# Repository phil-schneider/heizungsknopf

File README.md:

# Heizungsknopf – ein alter Gasofen bekommt einen Wochenplan

<table>
  <tr>
    <td align="center" valign="top" width="50%"></td>
    <td align="center" valign="top" width="50%"></td>
  </tr>
  <tr>
    <td align="center"><em>Heute: das Gasventil mit dem Drehknopf (✱ und 1–7)</em></td>
    <td align="center"><em>So soll es aussehen: Fotomontage mit dem Motoraufsatz (Erläuterung der Farben im Bild)</em></td>
  </tr>
</table>

Ein kleiner Motor dreht den Thermostatknopf eines Gas-Raumheizers, gesteuert von einem WLAN-Chip mit Wochenplan.
Am Ofen selbst wird nichts verändert: Der Aufsatz wird nur auf den vorhandenen Drehknopf gesteckt und lässt sich jederzeit wieder abziehen.

> [!WARNING]
> **Dieses Projekt ist noch in der Umsetzung und ungetestet.**
> Bisher wurde nichts davon gebaut oder am Ofen ausprobiert. Wer jetzt nachbaut, baut einen Entwurf nach.

## Projektstatus (Stand: November 2026)

| Bereich | Status |
|---|---|
| Idee und Messungen am Ofen | ✅ fertig |
| Platinen (Hauptplatine, Bedienteil) | ✅ entworfen · 📦 bestellt, noch nicht geliefert |
| Gehäuse und Motoraufsatz (3D-Druck) | ✅ entworfen · 📦 bestellt, noch nicht geliefert |
| Firmware | 🛠️ erste Version, muss an den Motoraufsatz angepasst werden |
| Zusammenbau | ⏳ noch nicht begonnen |
| Test am Ofen | ⏳ noch nicht begonnen |

Was noch fehlt, steht unter [Offene Punkte](#offene-punkte).

---

## Inhalt

1. [Projektstatus](#projektstatus-stand-november-2026)
2. [Warum gibt es dieses Projekt?](#warum-gibt-es-dieses-projekt)
3. [Was ist das Ziel?](#was-ist-das-ziel)
4. [Wie alles zusammenhängt](#wie-alles-zusammenhängt)
5. [Was liegt in diesem Repository?](#was-liegt-in-diesem-repository)
6. [Wie die einzelnen Teile funktionieren](#wie-die-einzelnen-teile-funktionieren)
7. [Nachbauen Schritt für Schritt](#nachbauen-schritt-für-schritt)
8. [Sicherheit](#sicherheit)
9. [Offene Punkte](#offene-punkte)
10. [Begriffe kurz erklärt](#begriffe-kurz-erklärt)

---

## Warum gibt es dieses Projekt?

Viele ältere Gas-Raumheizer (Gasöfen, Konvektoren) haben nur einen Drehknopf am Gasventil: ✱ für die Zündflamme und 1 bis 7 für die Temperatur. Eine Uhr oder einen Zeitplan gibt es nicht. Wer morgens in ein warmes Zimmer kommen will, muss abends den Knopf hochdrehen und heizt die ganze Nacht durch, oder er steht früh auf und dreht von Hand.

Moderne Thermostate kann man an so einen Ofen nicht einfach anschließen, und am Gasventil selbst darf und soll man als Laie nichts umbauen. Der einfachste sichere Weg ist deshalb: **Man lässt den Ofen, wie er ist, und dreht nur den Knopf automatisch**, so wie es ein Mensch auch tun würde.

## Was ist das Ziel?

- Der Ofen heizt nach einem **Wochenplan**, z. B. morgens um 6 Uhr auf Stufe 5, tagsüber Stufe 2, abends wieder Stufe 5.
- Man kann die Stufe jederzeit **am Ofen** (zwei Tasten und ein Display) oder **im Browser** (Handy, PC) ändern.
- Zusätzlich gibt es **Boost** (für eine Weile wärmer) und einen **Urlaubsmodus** (niedrige Stufe bis zu einem Rückkehrtag).
- Es braucht **keine Cloud und kein Home Assistant**. Der Knopf hat eine eigene kleine Webseite im Heimnetz.
- **Nichts am Gasofen wird umgebaut.** Der Motoraufsatz steckt auf dem Original-Knopf. Zieht man ihn ab, ist alles wie vorher.

---

## Wie alles zusammenhängt

Das System besteht aus **drei Baugruppen**, die mit Kabeln verbunden sind:

```mermaid
flowchart LR
    NT["12-V-Netzteil"] --> HP

    subgraph HP["Hauptplatine (im eigenen Gehäuse, neben dem Ofen)"]
        ESP["ESP32-C3<br/>WLAN, Uhr, Wochenplan"]
        TMC["TMC2209<br/>Motortreiber"]
        ESP --> TMC
    end

    BT["Bedienteil (an der Gittertür)<br/>Display · Tasten + und − · Raumtemperatur"]
    HP <-->|"normales Netzwerkkabel<br/>(RJ45, 1:1)"| BT

    TMC -->|"Motorkabel, 4 Adern"| MA

    subgraph MA["Motoraufsatz (auf dem Drehknopf)"]
        M["Schrittmotor NEMA17"] --> R["Ritzel"] --> Z["Kappe mit Zahnkranz"] --> K["Original-Drehknopf<br/>am Gasventil"]
    end

    DS["Ofenfühler DS18B20<br/>(optional)"] --> HP
    HANDY["Handy / PC im WLAN"] -.->|"Browser"| ESP
```

Falls das Diagramm nicht angezeigt wird, hier dasselbe als Skizze:

```
  12 V ──► ┌──────────────────┐   Netzwerkkabel   ┌─────────────────────┐
           │  HAUPTPLATINE    │◄─────────────────►│  BEDIENTEIL         │
 WLAN ◄──► │  ESP32-C3        │   (RJ45, 1:1)     │  Display, + / −,    │
           │  Motortreiber    │                   │  Temperatursensor   │
           └────────┬─────────┘                   └─────────────────────┘
                    │ Motorkabel (4 Adern)
                    ▼
           ┌──────────────────┐
           │  MOTORAUFSATZ    │   Motor ─► Ritzel ─► Zahnkranz-Kappe ─► Drehknopf
           └──────────────────┘
```

**So läuft es im Alltag ab:** Die Hauptplatine kennt die Uhrzeit (aus dem Internet) und den Wochenplan. Ist es Zeit für eine neue Stufe, dreht der Motor über zwei Zahnräder den Knopf auf die richtige Position. Das Display am Bedienteil zeigt die aktuelle Stufe, die Raumtemperatur und den nächsten Wechsel. Drückt man + oder −, dreht der Knopf sofort weiter, und diese Einstellung gilt bis zum nächsten Eintrag im Wochenplan.

---

## Was liegt in diesem Repository?

| Ordner | Inhalt | Wofür? |
|---|---|---|
| [`platinen/hauptplatine/`](platinen/hauptplatine) | `hauptplatine_Gerber.zip`, `hauptplatine_BOM_JLCPCB.csv`, `hauptplatine_CPL_JLCPCB.csv`, `hauptplatine.kicad_pcb` | Hauptplatine bestellen (fertig bestückt) oder in KiCad ansehen |
| [`platinen/bedienteil/`](platinen/bedienteil) | dieselben vier Dateien für das Bedienteil | Bedienplatine bestellen |
| [`3d-druck/stl/`](3d-druck/stl) | 12 STL-Dateien | Gehäuse und Motoraufsatz bei einem Druckdienst drucken lassen |
| [`3d-druck/step/`](3d-druck/step) | dieselben 12 Teile als STEP | Teile in einem CAD-Programm ansehen oder anpassen |
| [`firmware/`](firmware) | `heizung.yaml`, `heizung_logik.h`, `heizung_ui.js`, `secrets.example.yaml` | Software für den ESP32 (ESPHome) |
| [`bilder/`](bilder) | Vorschaubilder der Platinen und Druckteile | für diese Anleitung |

Was die Dateiendungen bedeuten, steht unten unter [Begriffe kurz erklärt](#begriffe-kurz-erklärt).

---

## Wie die einzelnen Teile funktionieren

### 1. Der Motoraufsatz: Wie der Knopf gedreht wird

Der Ofen hat ein Gasventil vom Typ **SIT 710 Minisit ECO**. Sein Drehknopf (Ø 35,7 mm, 19,4 mm hoch, 16 kleine Rippen am Rand) dreht von ✱ bis 7 um etwa **295°**, an beiden Enden ist ein fester Anschlag.

Die naheliegende Idee, den Motor einfach oben auf den Knopf zu setzen, passt nicht: Über dem Knopf sind nur **40,5 mm Platz** bis zu einem Querträger. Deshalb wird über Zahnräder gedreht:

```
        Seitenansicht, vereinfacht

     Ritzel ┐      ┌ Zahnkranz an der Kappe
            ▼      ▼
          ┌───┐ ┌───────────┐
          │▓▓▓│ │▓  Kappe  ▓│   ◄─ steckt auf dem Original-Knopf
     ═════╪═══╪═╪═══════════╪══════  Halter (liegt auf der Blende des Ventils)
          │   │ │   Knopf   │
      ┌───┴───┴─┐───────────────────
      │  Motor  │    Blende / Gasventil
      │ NEMA17  │
      └─────────┘
       (hängt vor der Blende)
```

- **Kappe mit Zahnkranz** (`motor_kappe_zahnkranz`): wird von oben auf den Knopf gesteckt. Innen hat sie 16 Nuten, in die die Rippen des Knopfs greifen, so dreht der Knopf mit, ohne zu rutschen. Außen sitzt ein Zahnkranz mit 34 Zähnen. Zwei kleine Madenschrauben sichern die Kappe zusätzlich.
- **Ritzel** (`motor_ritzel`): ein kleines Zahnrad mit 22 Zähnen auf der Motorwelle.
- **Motorhalter** (`motor_halter`): liegt wie ein Rahmen auf der Blende, ein Loch umschließt den Knopf und hält alles in Position. Der Motor hängt senkrecht davor. Zwei Stellschrauben drücken gegen die Vorderseite der Blende, damit der Halter waagerecht steht und nicht kippt.
- **Übersetzung:** 34 : 22, also etwa 1,55 : 1. Der Motor dreht etwas weiter als der Knopf, dafür hat er mehr Kraft am Knopf.
- **Von Hand bedienen:** Kappe nach oben abziehen (sie passt dabei noch unter den Querträger), oder bei ausgeschaltetem Motor einfach am Zahnkranz drehen.

Alle Maße wurden am echten Ofen gemessen. **Für einen anderen Ofen müssen die Teile angepasst werden** (z. B. in FreeCAD, Fusion oder Onshape über die STEP-Dateien).

### 2. Die Hauptplatine: das Gehirn (70 × 66 mm)

| Bauteil | Was es tut |
|---|---|
| **ESP32-C3-WROOM-02** (U1) | kleiner Computer mit WLAN. Darauf läuft die Firmware mit Uhr, Wochenplan und Webseite. |
| **TMC2209** (U2) | Motortreiber. Er bekommt vom ESP32 nur „einen Schritt weiter“ und „Richtung“ und erzeugt daraus die Ströme für den Motor. Er arbeitet sehr leise (StealthChop) und teilt jeden Motorschritt in 8 kleine Schritte. |
| **K7803** (U3) | Spannungswandler: macht aus 12 V die 3,3 V für die Elektronik. |
| **J1 „12V DC“** | Schraubklemme für das Netzteil (12 V, mindestens 1,5 A). |
| **J2 „USB“** | USB-C zum ersten Aufspielen der Firmware. **Dabei muss auch das 12-V-Netzteil angeschlossen sein.** |
| **J3 „MOTOR“** | Stecker (JST-XH, 4-polig) für den Schrittmotor. |
| **J6 „BEDIENTEIL“** | Netzwerkbuchse (RJ45) zum Bedienteil. |
| **J5 „DS18B20“** | optionaler Temperaturfühler am Ofen. |
| **J4 „ENDSTOP“**, **J7 „AS5600“** | Reserve für einen Endschalter bzw. Winkelsensor, wird im aktuellen Aufbau nicht gebraucht. |
| **SW1 RST, SW2 BOOT** | Neustart bzw. Flash-Modus (mit einer Büroklammer durch den Gehäusedeckel erreichbar). |
| **LED1 STAT, LED2 PWR** | Status und Betriebsspannung. |

Der Motorstrom ist auf etwa 0,7 A eingestellt (Widerstand R9 = 4,7 kΩ). Reicht die Kraft nicht, kann man R9 gegen 10 kΩ tauschen, das ergibt etwa 1,1 A.

<details>
<summary>Pinbelegung des ESP32 (für Fortgeschrittene)</summary>

| ESP32-Pin | Funktion |
|---|---|
| IO0 | STEP (Schritt) zum Motortreiber |
| IO1 | DIR (Richtung) |
| IO3 | ENN (Motortreiber ein/aus) |
| IO4 / IO21 | I2C SDA / SCL (Display und Sensor im Bedienteil) |
| IO2 / IO8 | Taste PLUS / Taste MINUS |
| IO5 | Endschalter (Reserve) |
| IO6 | DS18B20 |
| IO7 | Status-LED |
| IO10 / IO20 | UART zum TMC2209 |

</details>

### 3. Das Bedienteil: Display und Tasten am Ofen (48 × 62 mm)

<table>
  <tr>
    <td align="center" valign="top" width="50%"></td>
    <td align="center" valign="top" width="50%"></td>
  </tr>
  <tr>
    <td align="center"><em>So soll die Bedieneinheit aussehen (gerendert aus dem 3D-Modell, außen 80,5 × 124 × 25 mm)</em></td>
    <td align="center"><em>Die Bedienplatine darin</em></td>
  </tr>
</table>

- **Zwei große Taster** (12 × 12 mm): oben PLUS, darunter MINUS.
- **SHT40**: misst Raumtemperatur und Luftfeuchte.
- **J2 „OLED“**: Anschluss für ein 2,42-Zoll-OLED-Display (128 × 64 Pixel, Controller SSD1309, I2C). Das Display wird separat gekauft.
- **J1**: Netzwerkbuchse zur Hauptplatine.

**Was das Display anzeigt:** Groß die aktuelle Stufe mit einem Balken, rechts die Raumtemperatur, unten der nächste Wechsel laut Wochenplan oder ein aktiver Boost bzw. Urlaub. Hält man beide Tasten gleichzeitig, öffnet sich ein kleines Menü.

Die Bilder sind aus der Display-Programmierung der Firmware nachgebildet, mit derselben Schrift und denselben Positionen. Das echte Display kann je nach Modell etwas anders wirken.

Das Gehäuse des Bedienteils wird an die **Gittertür vor dem Ofen** geklemmt: Eine Gegenplatte kommt hinter das Gitter, der Gitterhalter davor, zwei Schrauben ziehen beide zusammen. Danach schiebt man das Gehäuse von oben auf eine Schiene (Schwalbenschwanz) am Halter. Zum Abnehmen zieht man es einfach nach oben ab.
Der Halter ist für ein Gitter aus aneinanderliegenden Ringen gebaut (Ring-Abstand 33,2 mm). Bei einem anderen Gitter muss er angepasst werden.

### 4. Die Verbindung: ein normales Netzwerkkabel

Hauptplatine und Bedienteil sind mit einem **handelsüblichen Netzwerk-Patchkabel** verbunden. Es wird aber **kein Netzwerk** darüber betrieben, das Kabel trägt nur Strom, die Tastensignale und die Display-Daten. Wichtig:

- Das Kabel muss **1:1 belegt** sein (normales Patchkabel, **kein** Crossover-Kabel).
- Es sollte **kürzer als 3 m** sein.
- **Niemals** einen Router, Switch oder PC an diese Buchsen anschließen.

<details>
<summary>Belegung der RJ45-Buchse</summary>

1 SCL · 2 GND · 3 SDA · 4 3,3 V · 5 GND · 6 GND · 7 PLUS · 8 MINUS

</details>

### 5. Die Gehäuse und Druckteile

Alle Teile werden bei einem **3D-Druckdienst** gedruckt. Material: **ASA** (FDM-Druck). ASA hält Temperaturen bis etwa 90 °C aus; **PLA ist ungeeignet**, weil es in der Nähe des Ofens weich wird.

| Datei | Stück | Farbe | Baugruppe | Größe (mm) |
|---|---|---|---|---|
| `motor_kappe_zahnkranz.stl` | 1 | schwarz | Motoraufsatz | 54 × 54 × 16,5 |
| `motor_ritzel.stl` | 1 | schwarz | Motoraufsatz | 36 × 36 × 13,8 |
| `motor_halter.stl` | 1 | schwarz | Motoraufsatz | 66 × 89 × 24 |
| `schale.stl` | 1 | schwarz | Bedienteil | 80,5 × 124 × 25 |
| `rueckdeckel.stl` | 1 | schwarz | Bedienteil | 75 × 118,5 × 12 |
| `gitterhalter.stl` | 1 | schwarz | Bedienteil | 44 × 76 × 12,5 |
| `gitter_gegenplatte.stl` | 1 | schwarz | Bedienteil | 40 × 73 × 22 |
| `displayklammer.stl` | **2** | schwarz | Bedienteil | 10 × 10,5 × 1,5 |
| `taste_plus.stl` | 1 | weiß | Bedienteil | 15,5 × 15,5 × 10,9 |
| `taste_minus.stl` | 1 | weiß | Bedienteil | 15,5 × 15,5 × 10,9 |
| `hp_wanne.stl` | 1 | schwarz | Gehäuse Hauptplatine | 76 × 97 × 29 |
| `hp_deckel.stl` | 1 | schwarz | Gehäuse Hauptplatine | 76 × 72 × 22 |

**Hinweise für den Druckdienst** (meist gibt es dafür ein Notizfeld):

- Füllung (Infill) mindestens 40 %, Wände mindestens 3 Linien.
- `motor_kappe_zahnkranz` und `motor_ritzel`: flach liegend drucken (Zähne senkrecht zur Bauplatte), Füllung 60–100 %.
- `displayklammer`: flach liegend, 100 % Füllung.
- Tipp: eine zweite Kappe als Ersatz mitbestellen. Wie stramm sie auf dem Knopf sitzt, ist nur aus Fotos geschätzt.

Die Symbole + und − sind 0,8 mm tief in die weißen Tasten eingraviert und können mit Acryllack oder einem Lackstift schwarz ausgelegt werden.

Bei den Konstruktionen wurde per Computer geprüft, dass sich keine Teile überschneiden, auch nicht beim Drehen der Kappe über 360° und beim Aufschieben des Bedienteils. Die Toleranzen sind für FDM-Druck ausgelegt.

### 6. Die Firmware: die Software auf dem ESP32

Die Firmware ist mit **[ESPHome](https://esphome.io)** gebaut. ESPHome ist ein kostenloses Werkzeug: Man beschreibt in einer YAML-Datei, was der Chip tun soll, und ESPHome macht daraus ein fertiges Programm und spielt es auf.

Die Firmware besteht aus drei Dateien, die im selben Ordner liegen müssen:

- `heizung.yaml`: die Hauptdatei (Pins, Motor, Sensoren, Display, Menü, Webseite)
- `heizung_logik.h`: Wochenplan-Berechnung
- `heizung_ui.js`: die eigene Weboberfläche

**Was sie kann:**

- **Wochenplan:** pro Wochentag bis zu 6 Wechsel, eingetragen als Text, z. B. `06:00=5 08:30=2 17:00=5 22:30=1` (Uhrzeit = Stufe).
- **Manuell übersteuern** mit + / − am Bedienteil oder im Browser. Das gilt bis zum nächsten Eintrag im Plan.
- **Boost:** für eine einstellbare Dauer auf eine einstellbare Stufe (im Browser auch „+30 Minuten“).
- **Urlaub:** eine eigene, meist niedrige Stufe für eine Anzahl Tage; ab einer einstellbaren Uhrzeit am Rückkehrtag wird wieder normal geheizt.
- **Menü am Bedienteil:** beide Tasten gleichzeitig halten.
- **Weboberfläche** mit Login, aufgeteilt in Bedienung, Wochenplan, Einstellungen und Diagnose. Sie zeigt auch Raumtemperatur, Luftfeuchte und (falls angeschlossen) die Ofentemperatur.
- **Uhrzeit** kommt automatisch aus dem Internet (Zeitzone Europe/Zurich, in `heizung.yaml` änderbar).
- **Fernzugriff von unterwegs** bitte nur über ein VPN (z. B. WireGuard am Router oder Tailscale), **nicht** über eine Portweiterleitung im Router.

**So sieht die Weboberfläche aus:** Man öffnet sie im Browser auf dem Handy oder PC (`http://heizung.local`). Auf der Startseite stellt man die Stufe ein und sieht dieselbe Anzeige wie am Display. Darunter folgen Boost, Urlaub und der Wochenplan. Tippt man auf einen Tag, kann man dessen Wechsel bearbeiten und auf andere Tage übernehmen.

Die Screenshots sind mit der echten Weboberfläche aus `firmware/heizung_ui.js` aufgenommen, aber mit simulierten Gerätedaten, weil die Hardware noch nicht läuft. Ist das Handy auf helles Design eingestellt, erscheint die Oberfläche hell.

---

## Nachbauen Schritt für Schritt

> Bitte vorher [Sicherheit](#sicherheit) und [Offene Punkte](#offene-punkte) lesen. Der Aufbau ist noch nicht erprobt.

### Schritt 1: Prüfen, ob der eigene Ofen passt

Der Motoraufsatz ist für ein **SIT-710-Minisit-Ventil** mit genau diesem Knopf ausgemessen. Vergleiche vor dem Bestellen:

- Knopf-Ø über die Rippen etwa 35,7 mm, 16 Rippen, Knopfhöhe 19,4 mm über der Blende
- über der Blende mindestens 40,5 mm frei
- vor der Blende Platz für den hängenden Motor (etwa 50 mm nach unten)
- Drehweg ✱ → 7 etwa 295° mit festen Anschlägen

Passt etwas nicht, die STEP-Dateien in einem CAD-Programm anpassen.

### Schritt 2: Platinen bestellen (fertig bestückt, z. B. bei JLCPCB)

Für jede der beiden Platinen:

1. Auf der Seite des Platinenherstellers die Datei **`…_Gerber.zip`** hochladen. Größe und Lagenzahl (2 Lagen) werden automatisch erkannt. Die übrigen Standardeinstellungen passen.
2. **Bestückung** (bei JLCPCB „PCB Assembly“) einschalten, Seite **Top**.
3. Die **Stückliste** `…_BOM_JLCPCB.csv` und die **Positionsdatei** `…_CPL_JLCPCB.csv` hochladen.
4. In der Vorschau prüfen, ob alle Bauteile richtig sitzen und richtig herum gedreht sind.
5. **Achtung RJ45-Buchse:** Die Buchse 54602-908LF (J6 auf der Hauptplatine, J1 auf dem Bedienteil) war bei JLCPCB nicht verfügbar und wurde nicht bestückt. Dann die Buchse separat kaufen (z. B. bei Conrad, Mouser, Digikey) und selbst einlöten. Sie hat nur Durchsteck-Pins und ist leicht zu löten.

Hersteller fertigen meist eine Mindestmenge (oft 5 Platinen), bestücken lassen kann man auch weniger.

### Schritt 3: Druckteile bestellen

1. Alle 12 STL-Dateien aus [`3d-druck/stl/`](3d-druck/stl) bei einem Druckdienst hochladen (z. B. Craftcloud, JLC3DP oder ein lokaler Anbieter).
2. Material **ASA**, Verfahren **FDM**, Farben und Stückzahlen wie in der [Tabelle oben](#5-die-gehäuse-und-druckteile). Die Displayklammer wird **2×** gebraucht.
3. Die Druckhinweise ins Notizfeld kopieren.

### Schritt 4: Einkaufsliste für die übrigen Teile

| Teil | Menge | Hinweis |
|---|---|---|
| Schrittmotor NEMA17, 40 mm lang (z. B. 17HS4417L) | 1 | Welle Ø 5 mm |
| OLED-Display 2,42", I2C, SSD1309, 4 Anschlüsse | 1 | Platine ca. 70,3 × 48,2 mm |
| Netzteil 12 V, mindestens 1,5 A | 1 | mit offenen Kabelenden oder passendem Adapter für die Schraubklemme |
| Netzwerk-Patchkabel, 1:1, unter 3 m | 1 | kein Crossover |
| RJ45-Buchse 54602-908LF | 2 | nur falls nicht bestückt (siehe Schritt 2) |
| JST-XH-Stecker 4-polig mit Crimpkontakten | 1 | für das Motorkabel |
| Temperaturfühler DS18B20 mit Kabel + JST-XH 3-polig | 1 | optional |
| Gewindeeinsätze M3 × 5,7 (z. B. ruthex), Bohrung 4,0 mm | 19 | werden mit dem Lötkolben eingeschmolzen |
| Madenschrauben (Gewindestifte) M3 | 3 | 2 in der Kappe, 1 im Ritzel |
| Zylinderschrauben M3 (DIN 912) | siehe unten | |
| dünne Litzen | | für Display und Motor |

Schrauben M3 (DIN 912):

- 4 × M3 × 8: Motor am Halter
- 2 × M3 × 10 oder 12: Stellschrauben am Motorhalter
- 4 × M3 × 10: Deckel des Hauptplatinen-Gehäuses
- 2 × M3 × 10 oder 12: Displayklammern
- 2 × M3 × 16: Gitterhalter
- Rückdeckel des Bedienteils: 4 × ca. M3 × 12 und 2 × ca. M3 × 8 (Länge beim Zusammenbau prüfen)

### Schritt 5: Zusammenbauen

**Vorbereiten**

- Alle Gewindeeinsätze mit dem Lötkolben in die vorgesehenen Löcher drücken (Temperaturangabe des Herstellers beachten).
- Ggf. die RJ45-Buchsen einlöten.

**Bedienteil**

1. Am Display die Lötbrücke **D2 schließen** (ein Lötpunkt über beide Felder). Ohne sie antwortet das Display nicht richtig.
2. Vier Litzen direkt an die Lötpunkte an der linken kurzen Seite des Displays löten (GND, VCC, SCL, SDA) und an die gleichnamigen Stifte von **J2** auf der Bedienplatine.
   **Keinen Dupont-Stecker** auf J2 stecken: Er ist etwa 2,5 mm zu hoch für das Gehäuse.
3. Display von innen in die Schale legen, Glas nach vorne zum Fenster. Oben unter die zwei Haken schieben, unten mit den zwei Displayklammern festschrauben.
4. Tasten einsetzen, Bedienplatine auf die vier Dome legen, Rückdeckel aufschrauben.
5. Gegenplatte hinter das Gitter, Gitterhalter davor, mit 2 × M3 × 16 verschrauben. Gehäuse von oben auf die Schiene schieben.
   Das Kabel an der Scharnierseite der Tür mit etwas Schlaufe verlegen, damit die Tür noch aufgeht.

**Motoraufsatz**

1. Motor mit 4 × M3 × 8 von oben an den Halter schrauben, das Kabel zeigt dabei nicht zur Blende.
2. Ritzel auf die Motorwelle stecken und mit der Madenschraube auf der flachen Seite der Welle festziehen.
3. Halter von oben über den Knopf auf die Blende setzen. Die zwei Stellschrauben so weit eindrehen, dass der Halter waagerecht steht.
4. Kappe von oben auf den Knopf stecken und leicht drehen, bis Rippen und Zähne greifen. Die zwei Madenschrauben nur leicht anziehen.
5. Das dünne Kupferröhrchen des Thermostatfühlers (tritt rechts unter der Blende aus) dabei nicht knicken.

**Hauptplatine**

1. Motorlitzen in den JST-Stecker crimpen und an J3 stecken. Die Kabel laufen durch die Kerben im Wannenrand.
2. Platine in die Wanne legen, Deckel mit 4 × M3 × 10 aufschrauben.
3. Gehäuse mit Schrauben oder Kabelbindern an den drei Laschen befestigen, etwa 30–80 cm vom Knopf entfernt und nicht direkt über heißen Flächen.

### Schritt 6: Firmware aufspielen

1. ESPHome installieren, z. B. mit Python: `pip install esphome` (Anleitung: [esphome.io](https://esphome.io/guides/installing_esphome)).
2. Im Ordner `firmware/` die Datei `secrets.example.yaml` nach **`secrets.yaml`** kopieren und WLAN-Name, Passwörter und Web-Login eintragen.
   Diese Datei wird nie ins Repository hochgeladen.
3. Hauptplatine mit **12 V** versorgen und per **USB-C** mit dem PC verbinden.
4. Im Ordner `firmware/` ausführen: `esphome run heizung.yaml`
5. Danach im Browser `http://heizung.local` öffnen. Klappt das nicht, die IP-Adresse des Geräts „heizung“ in der Geräteliste des Routers nachsehen. Unter **Einstellungen → Mechanik** die Werte abgleichen. Alle Positionen zählen in Schritten ab dem Anschlag ✱ (etwa 6,9 Schritte pro Grad am Knopf). Startwerte: Position ✱ 20, Position Stufe 1 690, Schritte pro Stufe 220, maximale Position 2050, Referenz-Strom 50 %. Bleibt der Knopf bei der Referenzfahrt vor ✱ stehen, den Referenz-Strom in 10-%-Schritten erhöhen.
6. Spätere Updates gehen über WLAN, ohne USB-Kabel: entweder mit `esphome run heizung.yaml` aus dem gleichen Netz, oder direkt im Browser in der Weboberfläche unter **Einstellungen → Firmware-Update**. Dort eine Datei im **OTA-Format** hochladen (im ESPHome Device Builder: „Install“ → „Manual download“ → „OTA format“, Datei `….ota.bin`). Das ist praktisch, wenn ESPHome nicht im selben Netz läuft wie die Heizung.

**Ohne Python, mit dem ESPHome Device Builder von Home Assistant:** Die drei Dateien aus `firmware/` nach `/config/esphome/` kopieren und die Zeilen aus `secrets.example.yaml` unter „Secrets“ an die bestehende Datei anhängen (die Namen beginnen mit `heizung_` und kollidieren nicht mit anderen Geräten). Beim Gerät „Install“ → „Manual download“ → **„Factory format“** wählen. Die `.bin`-Datei dann am PC mit Chrome oder Edge auf [web.esphome.io](https://web.esphome.io) per USB aufspielen („Connect“ → „Install“).

**Motortest ohne Aufsatz:** Unter **Einstellungen → Motortest** den Schalter **Testmodus** einschalten. Dann macht die Firmware keine Referenzfahrt, und Wochenplan und Stufen bewegen den Motor nicht. Die aktuelle Stellung gilt als Nullpunkt. Auf der Startseite erscheint eine Karte „Motortest“ mit −90°, −10°, +10° und +90° (Grad am Knopf; der Motor selbst dreht 1,55-mal so weit), einem Feld für die Position in Prozent der maximalen Position, „Stopp“ und „Nullpunkt hier“. Die Tasten PLUS und MINUS am Bedienteil fahren im Testmodus je 10°. Strom und Tempo lassen sich einstellen. Im Testmodus gibt es keine Begrenzung auf den Drehbereich, deshalb nur ohne Aufsatz oder vorsichtig benutzen. Beim Ausschalten startet die normale Referenzfahrt. Auch für den Test braucht die Platine 12 V, über USB allein dreht der Motor nicht.

---

## Sicherheit

- **Nichts am Gasventil verändern.** Der Aufsatz dreht ausschließlich den vorhandenen Knopf, so wie ein Mensch. Alle Sicherheitseinrichtungen des Ofens (Thermostat, Flammenüberwachung) bleiben unverändert.
- Der Motor dreht nur zwischen **✱ und 7**. Er kann den Ofen weder zünden noch ganz ausschalten.
- Das Bedienteil hängt am Gitter vor dem Ofen und wird warm. Deshalb **ASA statt PLA**.
- Kabel nicht über heiße Flächen führen und nicht einklemmen.
- Wer unsicher ist: den Ofen vorher von einer Fachperson prüfen lassen.
- Nachbau auf eigene Verantwortung.

---

## Offene Punkte

Bevor das System wirklich im Alltag laufen kann, fehlt noch:

- **Firmware: Stufen immer aus derselben Richtung anfahren**, weil Kappe und Zahnräder etwas Spiel haben. Der Rest ist umgesetzt: Übersetzung 34 : 22 als Startwerte, Referenzfahrt ohne Endschalter (mit wenig Strom gegen den Anschlag ✱), Motor im Stillstand stromlos.
- **Erster Aufbau und Test** an echter Hardware, besonders:
  - ob die Kraft des Motors reicht, um den Knopf zu drehen (nicht gemessen),
  - ob der Knopf von ✱ nicht ohne Drücken weiter auf „Aus“ geht (die Referenzfahrt drückt gegen ✱) und welcher „Referenz Strom“ nötig ist, damit der Knopf von 7 aus sicher bis ✱ kommt,
  - wie gut die Kappe auf dem Knopf sitzt,
  - ob der Bildbereich des Displays genau im Fenster liegt.
- **Montageort** des Hauptplatinen-Gehäuses festlegen.
- **Fernzugriff** entscheiden (WireGuard, Tailscale oder Cloudflare Tunnel).

---

## Begriffe kurz erklärt

| Begriff | Bedeutung |
|---|---|
| **Gerber-Dateien** (`…_Gerber.zip`) | Die „Druckvorlage“ einer Platine: Kupferbahnen, Lötstopplack, Beschriftung, Bohrlöcher. Das ist die Datei, die der Platinenhersteller braucht. |
| **BOM** (Bill of Materials) | Stückliste: welche Bauteile auf die Platine kommen. Die Spalte „LCSC Part #“ ist die Bestellnummer beim Bauteillager von JLCPCB. |
| **CPL** (Component Placement List) | Positionsdatei: wo genau und wie gedreht jedes Bauteil sitzt. Damit bestückt die Maschine die Platine. |
| **`.kicad_pcb`** | Das Platinenlayout im kostenlosen Programm [KiCad](https://www.kicad.org) (Version 7). Zum Ansehen oder Ändern. |
| **STL** | 3D-Modell als Dreiecksnetz. Das Standardformat für 3D-Druckdienste. |
| **STEP** | 3D-Modell mit exakten Flächen. Besser geeignet, um ein Teil in einem CAD-Programm zu ändern. |
| **FDM** | 3D-Druck, bei dem geschmolzener Kunststoff Schicht für Schicht aufgetragen wird. |
| **ASA** | wetter- und hitzebeständiger Kunststoff (bis etwa 90 °C), ähnlich wie ABS. |
| **ESP32-C3** | kleiner, günstiger Mikrocontroller mit WLAN. |
| **ESPHome** | kostenloses Werkzeug, um ESP32-Firmware aus einer YAML-Beschreibung zu erzeugen. |
| **Schrittmotor (NEMA17)** | Motor, der sich in genauen kleinen Schritten dreht (200 pro Umdrehung). NEMA17 ist die Baugröße (42 × 42 mm). |
| **Motortreiber (TMC2209)** | Chip, der den Schrittmotor mit Strom versorgt und die Schritte erzeugt. |
| **Mikroschritt** | Der Treiber teilt jeden Motorschritt in kleinere Teilschritte (hier 8). Das macht die Bewegung leiser und feiner. |
| **I2C** | einfache Zwei-Draht-Verbindung zwischen Chips, hier für Display und Temperatursensor. |
| **RJ45 / Patchkabel** | der übliche Stecker und das Kabel für Netzwerkanschlüsse. Hier nur als praktisches 8-adriges Kabel genutzt. |
| **Gewindeeinsatz** | kleine Messinghülse mit Innengewinde, die heiß in Kunststoff gedrückt wird, damit Schrauben dauerhaft halten. |
| **Ritzel / Zahnkranz** | kleines bzw. großes Zahnrad eines Zahnradpaars. |

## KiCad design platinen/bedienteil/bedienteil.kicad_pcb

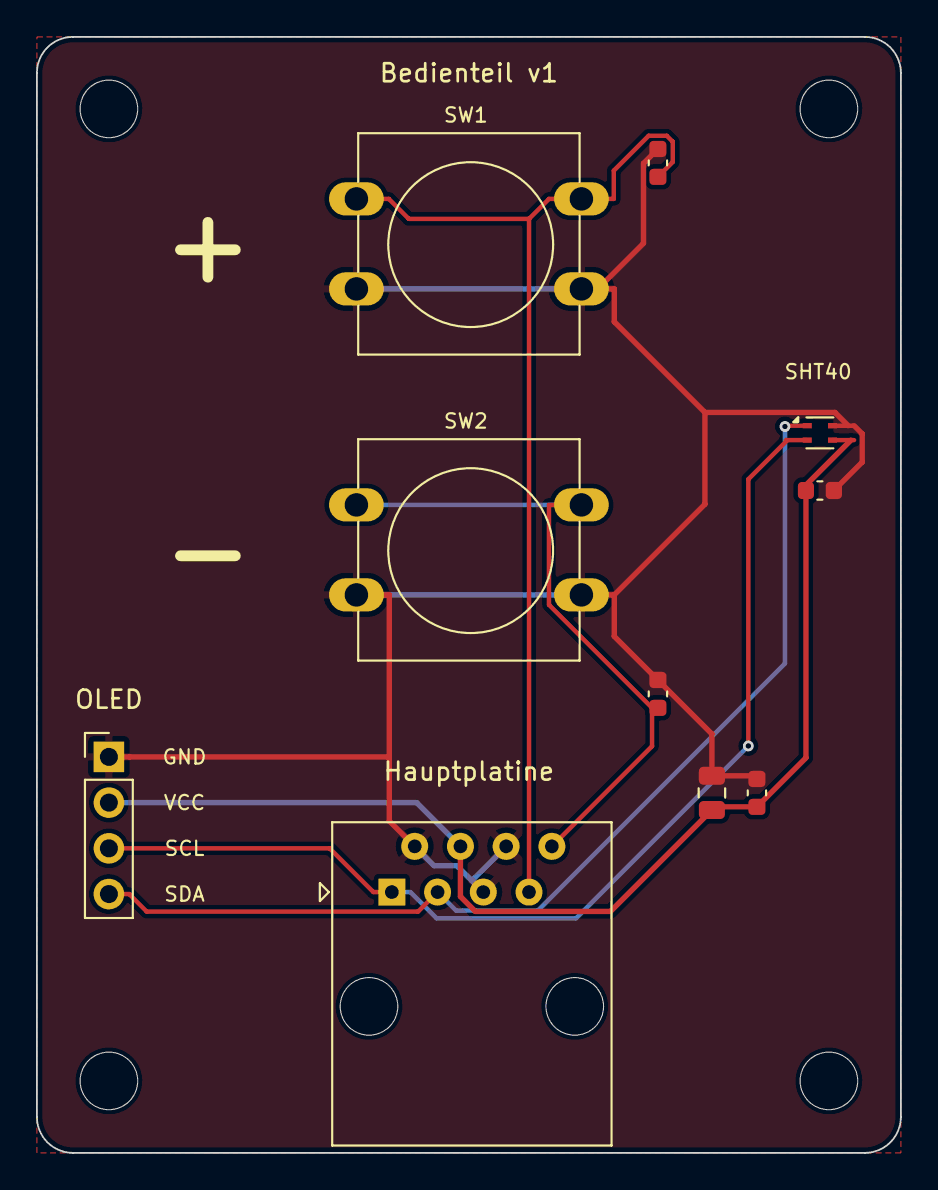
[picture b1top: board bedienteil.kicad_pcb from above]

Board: 2 copper layers, 48.0 x 62.0 mm, 14 parts (0 on the bottom side), 6 nets.

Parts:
C1, C3, C4, C5: 100nF; C_0603_1608Metric
C2: 10uF 25V; C_0805_2012Metric
H1, H2, H3, H4: M3; MountingHole_3.2mm_M3
J1: HAUPTPLATINE; RJ45_Amphenol_54602-x08_Horizontal
J2: OLED; PinHeader_1x04_P2.54mm_Vertical
SW1: PLUS; SW_PUSH-12mm
SW2: MINUS; SW_PUSH-12mm
U1: SHT40-AD1B-R2; Sensirion_DFN-4_1.5x1.5mm_P0.8mm_SHT4x_NoCentralPad

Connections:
+3V3: C1.1, C2.1, C3.1, J1.4, J2.2, U1.3
BTN_DN: C5.1, J1.8, SW2.1
BTN_UP: C4.1, J1.7, SW1.1
GND: C1.2, C2.2, C3.2, C4.2, C5.2, J1.2, J1.5, J1.6, J2.1, SW1.2, SW2.2, U1.4
I2C_SCL: J1.1, J2.3, U1.2
I2C_SDA: J1.3, J2.4, U1.1

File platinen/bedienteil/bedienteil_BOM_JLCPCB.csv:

Comment,Designator,Footprint,LCSC Part #,MPN,Qty
100nF,"C1,C3,C4,C5",C_0603_1608Metric,C14663,CC0603KRX7R9BB104,4
10uF 25V,C2,C_0805_2012Metric,C15850,CL21A106KAYNNNE,1
HAUPTPLATINE,J1,RJ45_Amphenol_54602-x08_Horizontal,C2847314,54602-908LF,1
OLED,J2,PinHeader_1x04_P2.54mm_Vertical,C492403,PZ254V-11-04P,1
PLUS / MINUS,"SW1,SW2",SW_PUSH-12mm,C720351,TS-1003-BR07016,2
SHT40-AD1B-R2,U1,Sensirion_DFN-4_1.5x1.5mm_P0.8mm_SHT4x_NoCentralPad,C2909890,SHT40-AD1B-R2,1

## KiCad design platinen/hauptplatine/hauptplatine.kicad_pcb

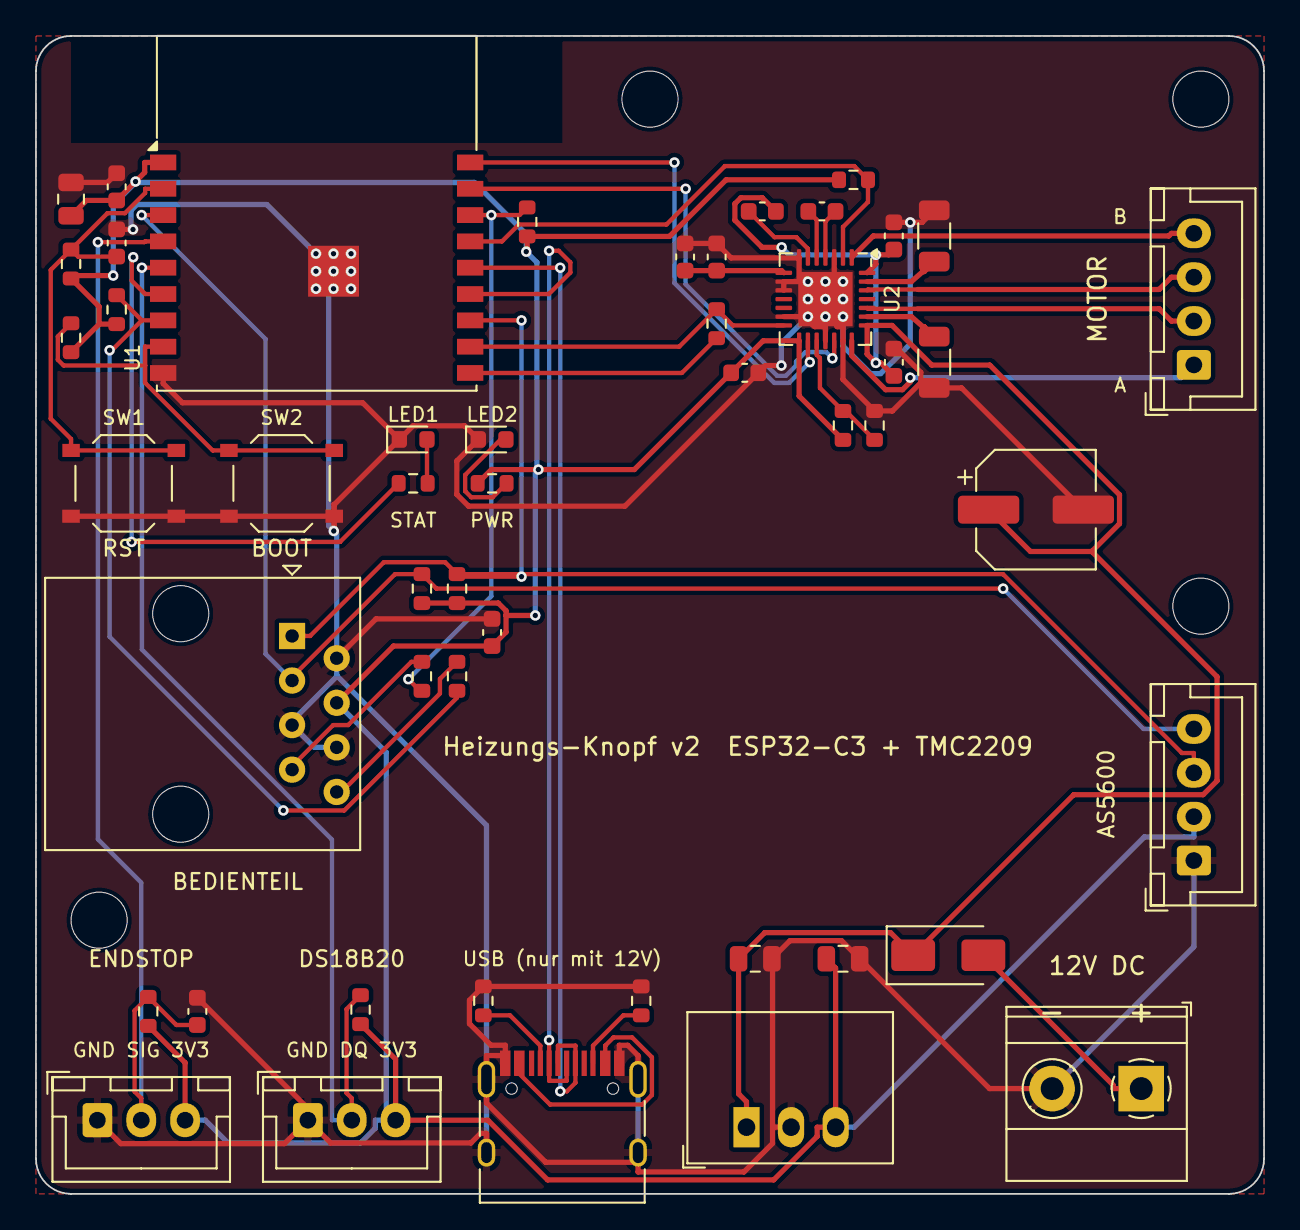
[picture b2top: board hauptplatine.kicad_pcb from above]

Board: 2 copper layers, 70.0 x 66.0 mm, 54 parts (0 on the bottom side), 38 nets.

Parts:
C1: 100uF 35V; CP_Elec_6.3x7.7
C2, C3, C7, C10, C12, C13, C14, C15: 100nF; C_0603_1608Metric
C4: 10uF 25V; C_0805_2012Metric
C5: 22uF 25V; C_0805_2012Metric
C6: 10uF; C_0805_2012Metric
C8: 1uF; C_0603_1608Metric
C9: 22nF; C_0603_1608Metric
C11: 4.7uF; C_0603_1608Metric
D1: SS34; D_SMA
H1, H2, H3, H4: M3; MountingHole_3.2mm_M3
J1: 12V IN; TerminalBlock_Phoenix_MKDS-1,5-2-5.08_1x02_P5.08mm_Horizont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
J2: USB-C; USB_C_Receptacle_HRO_TYPE-C-31-M-12
J3: MOTOR; JST_XH_B4B-XH-A_1x04_P2.50mm_Vertical
J4: ENDSTOP; JST_XH_B3B-XH-A_1x03_P2.50mm_Vertical
J5: DS18B20; JST_XH_B3B-XH-A_1x03_P2.50mm_Vertical
J6: BEDIENTEIL; RJ45_Amphenol_54602-x08_Horizontal
J7: AS5600; JST_XH_B4B-XH-A_1x04_P2.50mm_Vertical
LED1: gruen STATUS; LED_0603_1608Metric
LED2: gruen POWER; LED_0603_1608Metric
R1, R2, R3, R4, R8, R12, R14: 10k; R_0603_1608Metric
R5, R6: 5.1k; R_0603_1608Metric
R7, R15, R16, R19, R20: 1k; R_0603_1608Metric
R9, R13, R17, R18: 4.7k; R_0603_1608Metric
R10, R11: 0.12R; R_1206_3216Metric
SW1: RESET; SW_Push_1P1T_XKB_TS-1187A
SW2: BOOT; SW_Push_1P1T_XKB_TS-1187A
U1: ESP32-C3-WROOM-02-N4; ESP32-C3-WROOM-02
U2: TMC2209-LA-T; QFN-28-1EP_5x5mm_P0.5mm_EP3.1x3.1mm
U3: K7803-1000R3; Converter_DCDC_RECOM_R-78E-0.5_THT

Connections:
5VOUT: C11.1, C12.1, U2.8
+3V3: C5.1, C6.1, C7.1, C13.1, C15.1, J4.3, J5.3, J6.4, J7.2, R1.1, R2.1, R3.1, R4.1, R8.1, R12.1, R13.1, R14.1, R16.1, R17.1, R18.1, U1.1, U2.15, U3.3
BOOT: R2.2, SW2.1, U1.8
BRA: R10.2, U2.23
BRB: R11.1, U2.27
BTN_DN: R4.2, R20.1, U1.7
BTN_DN_X: J6.8, R20.2
BTN_UP: R3.2, R19.1, U1.16
BTN_UP_X: J6.7, R19.2
CC1: J2.A5, R5.1
CC2: J2.B5, R6.1
CPI: C9.1, U2.5
CPO: C9.2, U2.4
DIR: U1.17, U2.19
EN: C8.1, R1.2, SW1.1, U1.2
ENDSTOP: C14.1, J4.2, R12.2, U1.4
ENN: R14.2, U1.15, U2.2
GND: C1.2, C2.2, C3.2, C4.2, C5.2, C6.2, C7.2, C8.2, C11.2, C12.2, C13.2, C14.2, C15.2, J1.2, J2.A1, J2.A12, J2.B1, J2.B12, J2.S1, J4.1, J5.1, J6.2, J6.5, J6.6, J7.1, LED1.1, LED2.1, R5.2, R6.2, R9.2, R10.1, R11.2, SW1.2, SW2.2, U1.9, U1.19, U2.3, U2.7, U2.9, U2.10, U2.13, U2.18, U2.20, U2.29, U3.2
I2C_SCL: J6.1, J7.3, R18.2, U1.12
I2C_SDA: J6.3, J7.4, R17.2, U1.3
LED1_A: LED1.2, R15.2
LED2_A: LED2.2, R16.2
LED_STAT: R15.1, U1.6
OA1: J3.2, U2.24
OA2: J3.1, U2.21
OB1: J3.3, U2.26
OB2: J3.4, U2.1
ONEWIRE: J5.2, R13.2, U1.5
PDN_UART: R7.2, U1.11, U2.14
STEP: U1.18, U2.16
UART_TX: R7.1, U1.10
USB_DN: J2.A7, J2.B7, U1.13
USB_DP: J2.A6, J2.B6, U1.14
VBUS: J2.A4, J2.A9, J2.B4, J2.B9
VCP: C10.1, U2.6
VIN: D1.2, J1.1
VM: C1.1, C2.1, C3.1, C4.1, C10.2, D1.1, U2.22, U2.28, U3.1
VREF: R8.2, R9.1, U2.17

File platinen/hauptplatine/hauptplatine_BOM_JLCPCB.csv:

Comment,Designator,Footprint,LCSC Part #,MPN,Qty
100uF 35V,C1,CP_Elec_6.3x7.7,C65221,DV101M035E077ETR,1
100nF,"C10,C12,C13,C14,C15,C2,C3,C7",C_0603_1608Metric,C14663,CC0603KRX7R9BB104,8
4.7uF,C11,C_0603_1608Metric,C19666,CL10A475KO8NNNC,1
10uF 25V / 10uF,"C4,C6",C_0805_2012Metric,C15850,CL21A106KAYNNNE,2
22uF 25V,C5,C_0805_2012Metric,C45783,CL21A226MAQNNNE,1
1uF,C8,C_0603_1608Metric,C15849,CL10A105KB8NNNC,1
22nF,C9,C_0603_1608Metric,C21122,0603B223K500NT,1
SS34,D1,D_SMA,C8678,SS34,1
12V IN,J1,"TerminalBlock_Phoenix_MKDS-1,5-2-5.08_1x02_P5.08mm_Horizontal",C474952,KF128-5.08-2P-AA,1
USB-C,J2,USB_C_Receptacle_HRO_TYPE-C-31-M-12,C165948,TYPE-C-31-M-12,1
MOTOR / AS5600,"J3,J7",JST_XH_B4B-XH-A_1x04_P2.50mm_Vertical,C144395,B4B-XH-A(LF)(SN),2
ENDSTOP / DS18B20,"J4,J5",JST_XH_B3B-XH-A_1x03_P2.50mm_Vertical,C144394,B3B-XH-A(LF)(SN),2
BEDIENTEIL,J6,RJ45_Amphenol_54602-x08_Horizontal,C2847314,54602-908LF,1
gruen STATUS / gruen POWER,"LED1,LED2",LED_0603_1608Metric,C72043,19-217/GHC-YR1S2/3T,2
10k,"R1,R12,R14,R2,R3,R4,R8",R_0603_1608Metric,C25804,0603WAF1002T5E,7
0.12R,"R10,R11",R_1206_3216Metric,C309629,RL1206FR-070R12L,2
4.7k,"R13,R17,R18,R9",R_0603_1608Metric,C23162,0603WAF4701T5E,4
1k,"R15,R16,R19,R20,R7",R_0603_1608Metric,C21190,0603WAF1001T5E,5
5.1k,"R5,R6",R_0603_1608Metric,C23186,0603WAF5101T5E,2
RESET / BOOT,"SW1,SW2",SW_Push_1P1T_XKB_TS-1187A,C318884,TS-1187A-B-A-B,2
ESP32-C3-WROOM-02-N4,U1,ESP32-C3-WROOM-02,C2934560,ESP32-C3-WROOM-02-N4,1
TMC2209-LA-T,U2,QFN-28-1EP_5x5mm_P0.5mm_EP3.1x3.1mm,C2150710,TMC2209-LA-T,1
K7803-1000R3,U3,Converter_DCDC_RECOM_R-78E-0.5_THT,C111278,K7803-1000R3,1

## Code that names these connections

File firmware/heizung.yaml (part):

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#  Sensoren:     DS18B20 am Warmluftaustritt
#  Referenz:     ohne Endschalter – der Motor fährt mit reduziertem Strom gegen
#                den festen Anschlag ✱ des Knopfs (Motoraufsatz v0.3).
#                Der Stecker ENDSTOP (J4, GPIO5) bleibt frei.
#  Eigenständig, ohne Home Assistant. Weboberfläche: heizung_ui.js
#
#  Dateien im selben Ordner:  heizung.yaml · heizung_logik.h · heizung_ui.js · secrets.yaml
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
# ---------------------------------------------------------------------
# Schrittmotor (TMC2209 im STEP/DIR-Modus)
# Der sleep_pin schaltet den Treiber (ENN) ab, sobald das Ziel erreicht ist:
# im Stillstand ist der Motor stromlos und der Knopf lässt sich von Hand drehen.
# ---------------------------------------------------------------------
stepper:
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    step_pin: GPIO0
    dir_pin: GPIO1
    sleep_pin:
      number: GPIO3            # ENN: LOW = Treiber an
      inverted: true
    max_speed: ${speed} steps/s
    acceleration: 400 steps/s^2
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          static bool halten_p = false, halten_m = false;
          static uint32_t t_p = 0, t_m = 0, t_kombi = 0, t_rep = 0;
          const uint32_t ms = millis();
          const bool p = id(btn_up).state, m = id(btn_dn).state;

          if (p && m) {
            if (!kombi) { kombi = true; kombi_fertig = false; t_kombi = ms; }
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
